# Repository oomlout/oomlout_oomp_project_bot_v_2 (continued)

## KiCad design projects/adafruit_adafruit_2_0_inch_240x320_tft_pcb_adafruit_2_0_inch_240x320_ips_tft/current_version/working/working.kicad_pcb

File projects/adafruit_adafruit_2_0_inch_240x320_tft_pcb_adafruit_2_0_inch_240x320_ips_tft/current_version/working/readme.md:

# adafruit_2_0_inch_240x320_tft_pcb
 
## summary 
* id: adafruit_adafruit_2_0_inch_240x320_tft_pcb_adafruit_2_0_inch_240x320_ips_tft
* user: adafruit
* name: adafruit_2_0_inch_240x320_tft_pcb
* board: adafruit_2_0_inch_240x320_ips_tft
* repo: https://github.com/adafruit/Adafruit-2.0-inch-240x320-TFT-PCB

* src_file_repo_sch: 
* src_file_repo_sch_link: https://github.com/adafruit/Adafruit-2.0-inch-240x320-TFT-PCB/tree/master/
* full details link: https://github.com/oomlout/oomlout_oomp_project_bot_v_2/tree/main/projects/adafruit_adafruit_2_0_inch_240x320_tft_pcb_adafruit_2_0_inch_240x320_ips_tft/current_version/working  

## schematic  
  
[schematic (pdf)](working_schematic.pdf) 

## pcb  

[board (pdf)](working.pdf)  

## working_bom
| Id | Designator | Footprint | Quantity | Designation | Supplier and ref |  | None | 
| --- | --- | --- | --- | --- | --- | --- | --- | 
| 1 | U2 | SOT23-5 | 1 | AP2112K-3.3 |  |  | [''] | 
| 2 | R1 | 0805-NO | 1 | 10 |  |  | [''] | 
| 3 | Q1 | SOT23-R | 1 | BSS138 |  |  | [''] | 
| 4 | U$24 | PCBFEAT-REV-040 | 1 |  |  |  | [''] | 
| 5 | U3 | SOIC16 | 1 | 74HC4050D |  |  | [''] | 
| 6 | FID1,FID3,FID2 | FIDUCIAL_1MM | 3 | FIDUCIAL_1MM |  |  | [''] | 
| 7 | R8,R5,R2,R7 | 0805-NO | 4 | 10K |  |  | [''] | 
| 8 | U$4,U$3 | MOUNTINGHOLE_2.5_PLATED | 2 | MOUNTINGHOLE2.5 |  |  | [''] | 
| 9 | IC4 | SOT23 | 1 | APX803-SAG |  |  | [''] | 
| 10 | JP1 | 1X11_ROUND_76 | 1 |  |  |  | [''] | 
| 11 | C1,C3,C2 | 0805-NO | 3 | 10uF |  |  | [''] | 
| 12 | CN1 | MICROSD | 1 |  |  |  | [''] | 
| 13 | U$20 | ADAFRUIT_TEXT_30MM | 1 |  |  |  | [''] | 
| 14 | DISP1 | TFT_2.0IN_240X320_12P | 1 | DISP_LCD_GENERIC_SPI_2.0IN_240X320 |  |  | [''] | 

## bom_schematic
| Ref | Qnty | Value | Cmp name | Footprint | Description | Vendor | DNP | 
| --- | --- | --- | --- | --- | --- | --- | --- | 
| C1, C2, C3 | 3 | 10uF | CAP_CERAMIC0805-NOOUTLINE | working:0805-NO |  |  |  | 
| CN1 | 1 | MICROSD | MICROSD | working:MICROSD |  |  |  | 
| DISP1 | 1 | DISP_LCD_GENERIC_SPI_2.0IN_240X320 | DISP_LCD_GENERIC_SPI_2.0IN_240X320 | working:TFT_2.0IN_240X320_12P |  |  |  | 
| FID1, FID2, FID3 | 3 | FIDUCIAL_1MM | FIDUCIAL_1MM | working:FIDUCIAL_1MM |  |  |  | 
| IC4 | 1 | APX803-SAG | AXP083-SAG | working:SOT23 |  |  |  | 
| JP1 | 1 | HEADER-1X1176MIL | HEADER-1X1176MIL | working:1X11_ROUND_76 |  |  |  | 
| Q1 | 1 | BSS138 | MOSFET-NREFLOW | working:SOT23-R |  |  |  | 
| R1 | 1 | 10 | RESISTOR0805_NOOUTLINE | working:0805-NO |  |  |  | 
| R2, R5, R7, R8 | 4 | 10K | RESISTOR0805_NOOUTLINE | working:0805-NO |  |  |  | 
| U2 | 1 | AP2112K-3.3 | VREG_SOT23-5 | working:SOT23-5 |  |  |  | 
| U3 | 1 | 74HC4050D | 74HC4050D | working:SOIC16 |  |  |  | 
| U$3, U$4 | 2 | MOUNTINGHOLE2.5 | MOUNTINGHOLE2.5 | working:MOUNTINGHOLE_2.5_PLATED |  |  |  | 

## mounting_holes
| x | y | package | value | ref | size | 
| --- | --- | --- | --- | --- | --- | 
| 30.48 | 0.0 | MOUNTINGHOLE_2.5_PLATED | MOUNTINGHOLE2.5 | U$3 | m3 | 
| 0.0 | 0.0 | MOUNTINGHOLE_2.5_PLATED | MOUNTINGHOLE2.5 | U$4 | m3 |

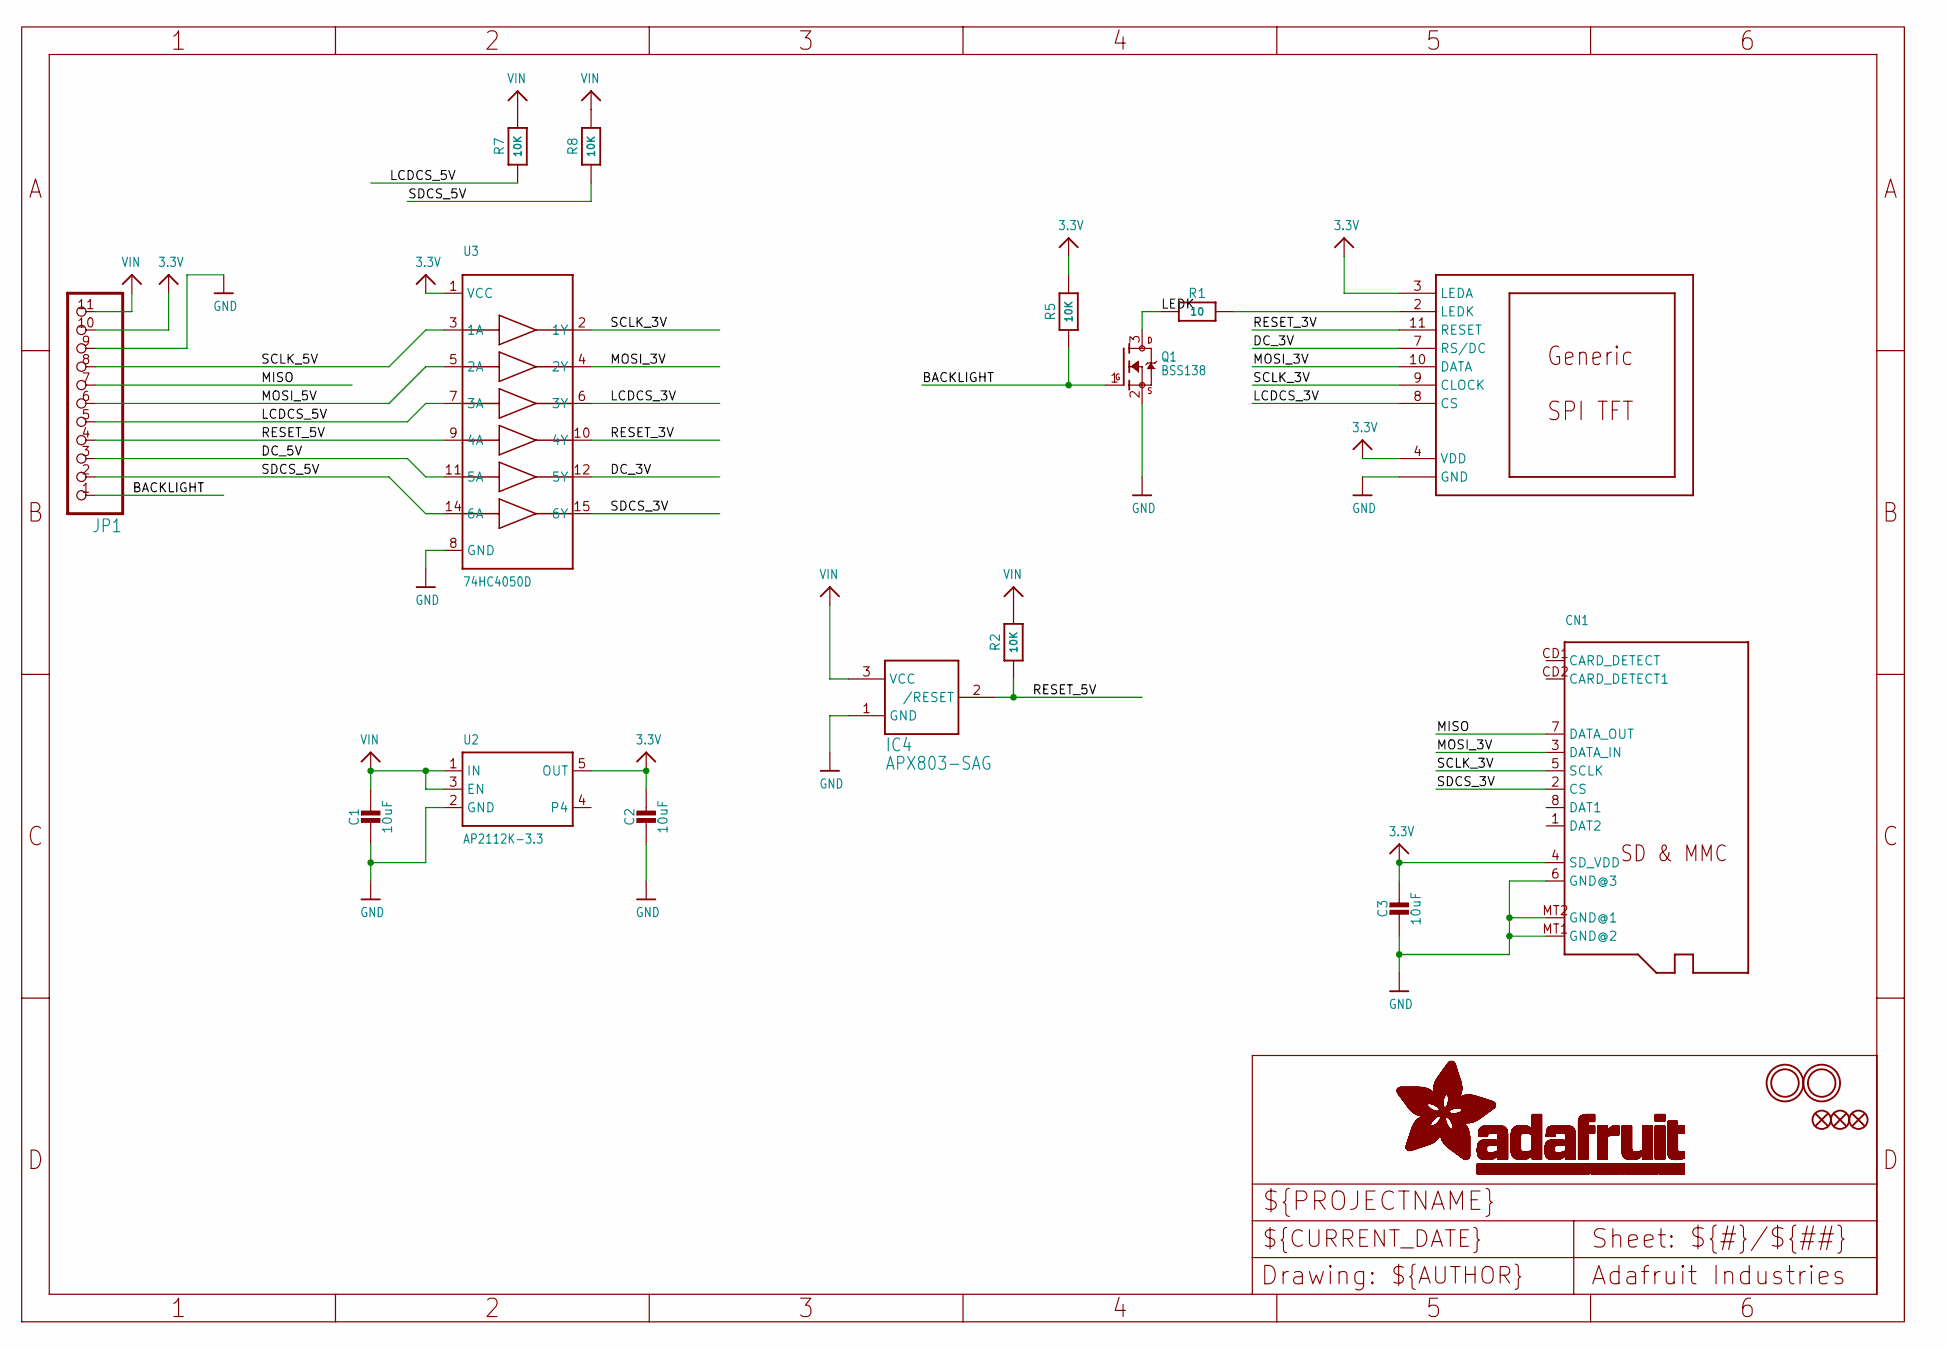
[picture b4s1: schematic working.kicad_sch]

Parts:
C1, C2, C3: 10uF; 0805-NO
CN1: MICROSD
DISP1: DISP_LCD_GENERIC_SPI_2.0IN_240X320; TFT_2.0IN_240X320_12P
FID1, FID2, FID3: FIDUCIAL_1MM
IC4: APX803-SAG; SOT23
JP1: HEADER-1X1176MIL; 1X11_ROUND_76
Q1: BSS138; SOT23-R
R1: 10; 0805-NO
R2, R5, R7, R8: 10K; 0805-NO
U2: AP2112K-3.3; SOT23-5
U3: 74HC4050D; SOIC16
U$3, U$4: MOUNTINGHOLE2.5; MOUNTINGHOLE_2.5_PLATED

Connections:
3.3V: C2.1, C3.1, CN1.4 (SD_VDD), DISP1.3 (LEDA), DISP1.4 (VDD), JP1.10, R5.2, U2.5 (OUT), U3.1 (VCC)
BACKLIGHT: JP1.1, Q1.1 (G), R5.1
DC_3V: DISP1.7 (RS/DC), U3.12 (5Y)
DC_5V: JP1.3, U3.11 (5A)
GND: C1.2, C2.2, C3.2, CN1.6 (GND@3), CN1.MT1 (GND@2), CN1.MT2 (GND@1), DISP1.1 (GND), DISP1.5 (GND), DISP1.6 (GND), DISP1.12 (GND), IC4.1 (GND), JP1.9, Q1.2 (S), U2.2 (GND), U3.8 (GND)
LCDCS_3V: DISP1.8 (CS), U3.6 (3Y)
LCDCS_5V: JP1.5, R7.1, U3.7 (3A)
LEDK: Q1.3 (D), R1.1
MISO: CN1.7 (DATA_OUT), JP1.7
MOSI_3V: CN1.3 (DATA_IN), DISP1.10 (DATA), U3.4 (2Y)
MOSI_5V: JP1.6, U3.5 (2A)
unnamed: DISP1.2 (LEDK), R1.2
RESET_3V: DISP1.11 (RESET), U3.10 (4Y)
RESET_5V: IC4.2 (/RESET), JP1.4, R2.1, U3.9 (4A)
SCLK_3V: CN1.5 (SCLK), DISP1.9 (CLOCK), U3.2 (1Y)
SCLK_5V: JP1.8, U3.3 (1A)
SDCS_3V: CN1.2 (CS), U3.15 (6Y)
SDCS_5V: JP1.2, R8.1, U3.14 (6A)
VIN: C1.1, IC4.3 (VCC), JP1.11, R2.2, R7.2, R8.2, U2.1 (IN), U2.3 (EN)

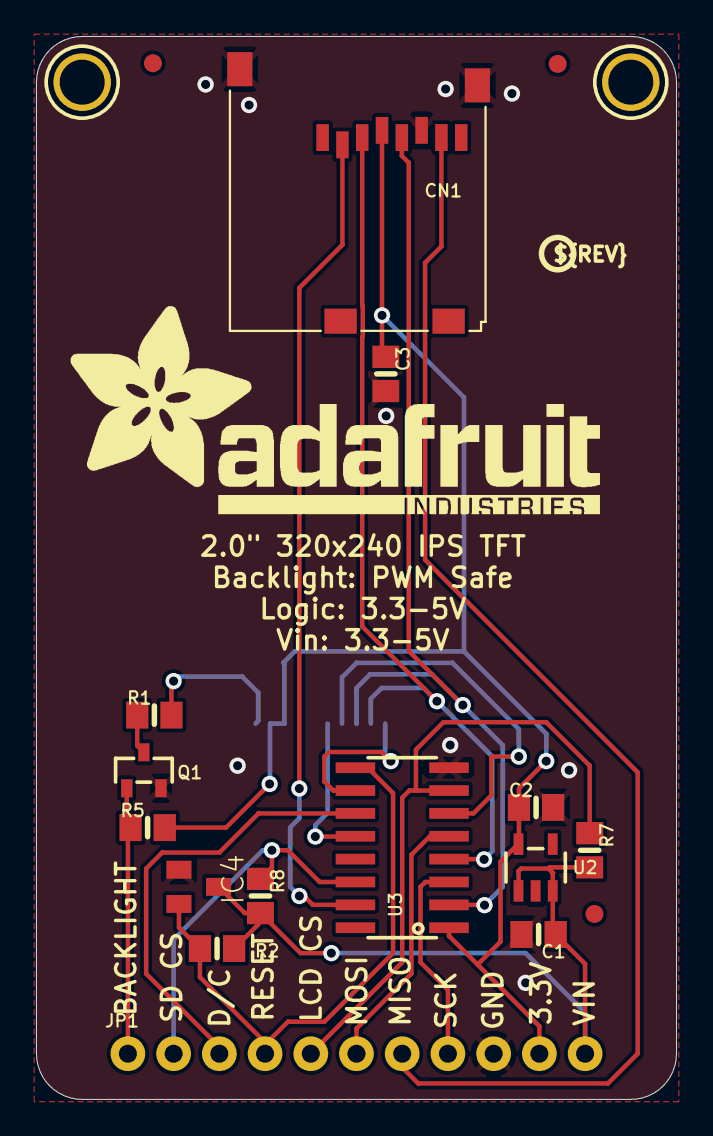
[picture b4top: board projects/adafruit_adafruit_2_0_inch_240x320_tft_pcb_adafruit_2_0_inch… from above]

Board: 2 copper layers, 35.6 x 59.1 mm, 22 parts (1 on the bottom side), 19 nets.

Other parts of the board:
U$20: ADAFRUIT_TEXT_30MM
U$24: PCBFEAT-REV-040

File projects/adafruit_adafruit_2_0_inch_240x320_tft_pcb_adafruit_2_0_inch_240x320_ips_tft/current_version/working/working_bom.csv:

"Id";"Designator";"Footprint";"Quantity";"Designation";"Supplier and ref";
1;"U2";"SOT23-5";1;"AP2112K-3.3";;;
2;"R1";"0805-NO";1;"10";;;
3;"Q1";"SOT23-R";1;"BSS138";;;
4;"U$24";"PCBFEAT-REV-040";1;"";;;
5;"U3";"SOIC16";1;"74HC4050D";;;
6;"FID1,FID3,FID2";"FIDUCIAL_1MM";3;"FIDUCIAL_1MM";;;
7;"R8,R5,R2,R7";"0805-NO";4;"10K";;;
8;"U$4,U$3";"MOUNTINGHOLE_2.5_PLATED";2;"MOUNTINGHOLE2.5";;;
9;"IC4";"SOT23";1;"APX803-SAG";;;
10;"JP1";"1X11_ROUND_76";1;"";;;
11;"C1,C3,C2";"0805-NO";3;"10uF";;;
12;"CN1";"MICROSD";1;"";;;
13;"U$20";"ADAFRUIT_TEXT_30MM";1;"";;;
14;"DISP1";"TFT_2.0IN_240X320_12P";1;"DISP_LCD_GENERIC_SPI_2.0IN_240X320";;;

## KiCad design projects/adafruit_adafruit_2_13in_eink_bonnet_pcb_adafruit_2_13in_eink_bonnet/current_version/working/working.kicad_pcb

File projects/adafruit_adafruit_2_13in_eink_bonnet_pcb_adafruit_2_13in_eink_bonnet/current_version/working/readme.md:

# adafruit_2_13in_eink_bonnet_pcb
 
## summary 
* id: adafruit_adafruit_2_13in_eink_bonnet_pcb_adafruit_2_13in_eink_bonnet
* user: adafruit
* name: adafruit_2_13in_eink_bonnet_pcb
* board: adafruit_2_13in_eink_bonnet
* repo: https://github.com/adafruit/Adafruit-2-13in-eInk-Bonnet-PCB

* src_file_repo_sch: 
* src_file_repo_sch_link: https://github.com/adafruit/Adafruit-2-13in-eInk-Bonnet-PCB/tree/master/
* full details link: https://github.com/oomlout/oomlout_oomp_project_bot_v_2/tree/main/projects/adafruit_adafruit_2_13in_eink_bonnet_pcb_adafruit_2_13in_eink_bonnet/current_version/working  

## schematic  
  
[schematic (pdf)](working_schematic.pdf) 

## pcb  

[board (pdf)](working.pdf)  

## working_bom
| Id | Designator | Footprint | Quantity | Designation | Supplier and ref |  | None | 
| --- | --- | --- | --- | --- | --- | --- | --- | 
| 1 | C3,C4,C23,C22 | 0805-NO | 4 | 1uF/25V |  |  | [''] | 
| 2 | R3,R5,R2,R6 | 0603-NO | 4 | 100K |  |  | [''] | 
| 3 | D2,D3,D1 | SOD-123 | 3 | MBR0540 |  |  | [''] | 
| 4 | C5 | 0805-NO | 1 | 4.7uF/25V |  |  | [''] | 
| 5 | U$28 | ADAFRUIT_TEXT_20MM | 1 |  |  |  | [''] | 
| 6 | C16,C24 | 0805-NO | 2 | 1uF |  |  | [''] | 
| 7 | C1,C15 | 0805-NO | 2 | 10uF/10V+ |  |  | [''] | 
| 8 | CONN2 | JST_SH4 | 1 | STEMMA_I2C_QT |  |  | [''] | 
| 9 | Q5 | SOT23-3 | 1 | IRLML0100 |  |  | [''] | 
| 10 | C2,C6 | 0805-NO | 2 | 1uF/10V |  |  | [''] | 
| 11 | R4 | 0805_10MGAP | 1 | 0.47ohm |  |  | [''] | 
| 12 | U$30 | STEMMAQT | 1 |  |  |  | [''] | 
| 13 | U$9 | PCBFEAT-REV-040 | 1 |  |  |  | [''] | 
| 14 | U$29 | THINKINK_1.25IN | 1 |  |  |  | [''] | 
| 15 | FID4,FID1,FID3,FID2 | FIDUCIAL_1MM | 4 | FIDUCIAL_1MM |  |  | [''] | 
| 16 | C21 | 0805-NO | 1 | 10ÂµF |  |  | [''] | 
| 17 | L1 | INDUCTOR_4X4MM_NR401 | 1 | 10uH |  |  | [''] | 
| 18 | SW3,SW4 | TACTILE_3X6MM | 2 |  |  |  | [''] | 
| 19 | RPI2 | PI_BONNET_SMT_NODIM | 1 | RASPBERRYPI_BPLUS_SMT_NODIM |  |  | [''] | 
| 20 | EINK1 | EINK_213IN_104X212 | 1 | EINK_24PIN_213IN |  |  | [''] | 

## bom_schematic
| Ref | Qnty | Value | Cmp name | Footprint | Description | Vendor | DNP | 
| --- | --- | --- | --- | --- | --- | --- | --- | 
| C1, C15 | 2 | 10uF/10V+ | CAP_CERAMIC0805-NOOUTLINE | working:0805-NO |  |  |  | 
| C2, C6 | 2 | 1uF/10V | CAP_CERAMIC0805-NOOUTLINE | working:0805-NO |  |  |  | 
| C3, C4, C22, C23 | 4 | 1uF/25V | CAP_CERAMIC0805-NOOUTLINE | working:0805-NO |  |  |  | 
| C5 | 1 | 4.7uF/25V | CAP_CERAMIC0805-NOOUTLINE | working:0805-NO |  |  |  | 
| C16, C24 | 2 | 1uF | CAP_CERAMIC0805-NOOUTLINE | working:0805-NO |  |  |  | 
| C21 | 1 | 10ÂµF | CAP_CERAMIC0805-NOOUTLINE | working:0805-NO |  |  |  | 
| CONN2 | 1 | STEMMA_I2C_QT | STEMMA_I2C_QT | working:JST_SH4 |  |  |  | 
| D1, D2, D3 | 3 | MBR0540 | DIODE-SCHOTTKYSOD-123 | working:SOD-123 |  |  |  | 
| EINK1 | 1 | EINK_24PIN_213IN | EINK_24PIN_213IN | working:EINK_213IN_104X212 |  |  |  | 
| FID1, FID2, FID3, FID4 | 4 | FIDUCIAL_1MM | FIDUCIAL_1MM | working:FIDUCIAL_1MM |  |  |  | 
| L1 | 1 | 10uH | INDUCTORNR401 | working:INDUCTOR_4X4MM_NR401 |  |  |  | 
| Q5 | 1 | IRLML2060TRPBF | IRLML2060TRPBF | working:SOT23-3 |  |  |  | 
| R2, R3, R5, R6 | 4 | 100K | RESISTOR_0603_NOOUT | working:0603-NO |  |  |  | 
| R4 | 1 | 0.47ohm | RESISTOR0805_10MGAP | working:0805_10MGAP |  |  |  | 
| RPI2 | 1 | RASPBERRYPI_BPLUS_SMT_NODIM | RASPBERRYPI_BPLUS_SMT_NODIM | working:PI_BONNET_SMT_NODIM |  |  |  | 
| SW3, SW4 | 2 | SWITCH_PUSHBUTTON_3.5X6MM | SWITCH_PUSHBUTTON_3.5X6MM | working:TACTILE_3X6MM |  |  |  |

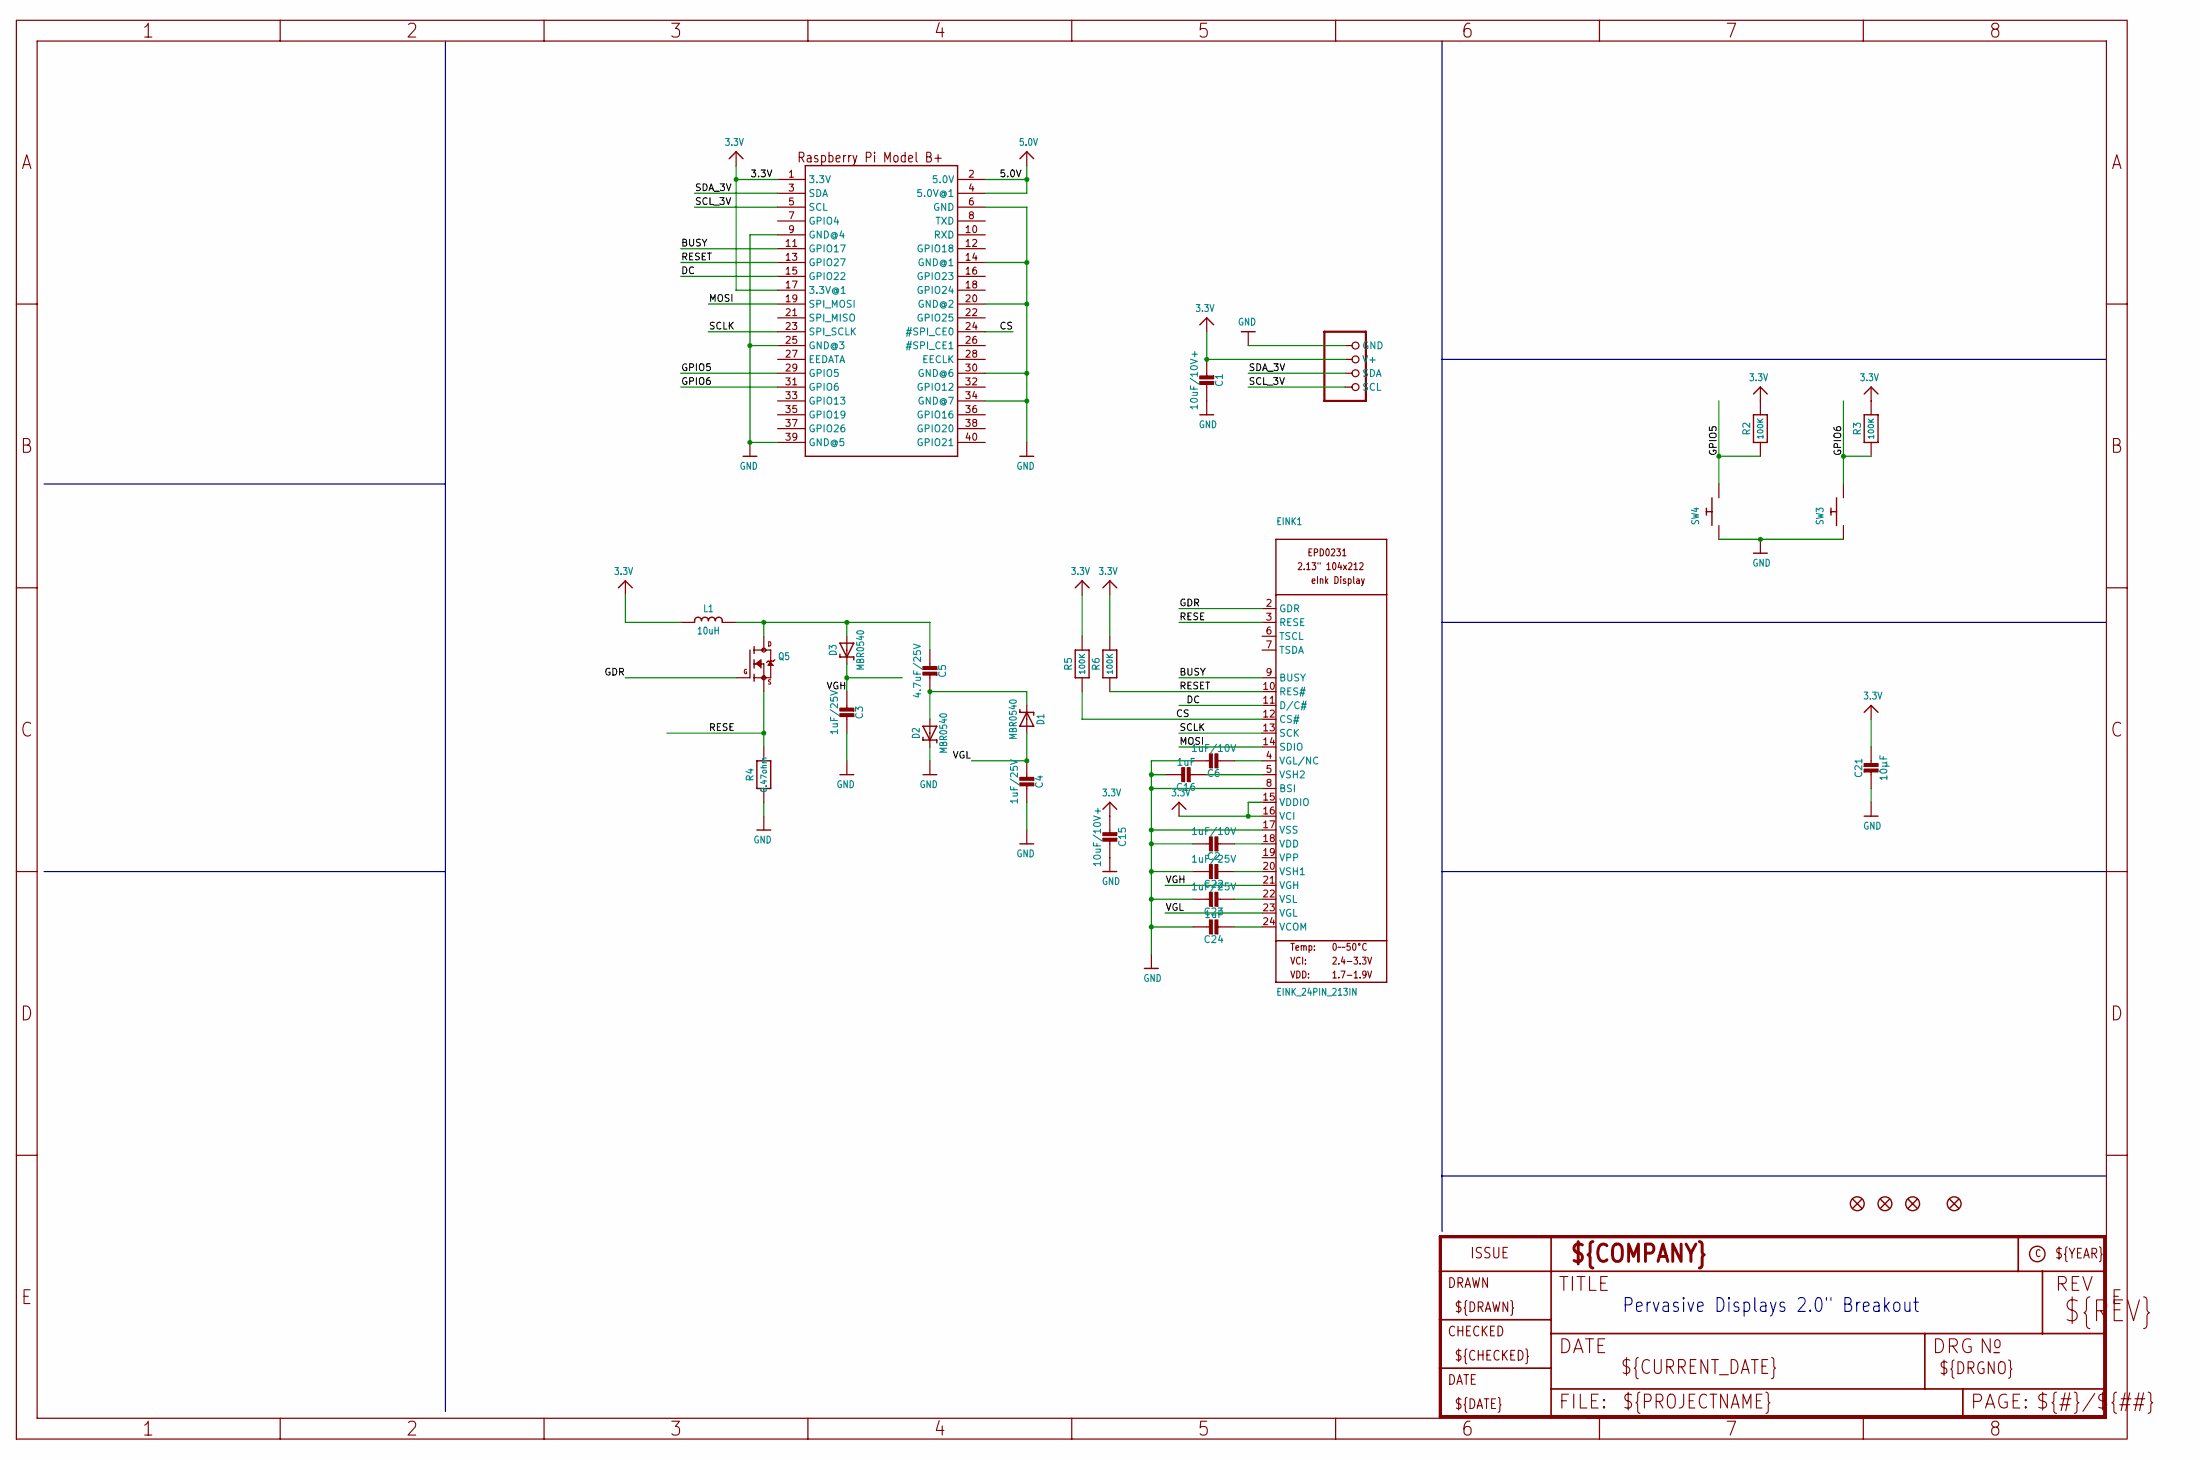
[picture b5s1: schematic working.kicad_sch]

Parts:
C1, C15: 10uF/10V+; 0805-NO
C2, C6: 1uF/10V; 0805-NO
C3, C4, C22, C23: 1uF/25V; 0805-NO
C5: 4.7uF/25V; 0805-NO
C16, C24: 1uF; 0805-NO
C21: 10µF; 0805-NO
CONN2: STEMMA_I2C_QT; JST_SH4
D1, D2, D3: MBR0540; SOD-123
EINK1: EINK_24PIN_213IN; EINK_213IN_104X212
FID1, FID2, FID3, FID4: FIDUCIAL_1MM
L1: 10uH; INDUCTOR_4X4MM_NR401
Q5: IRLML2060TRPBF; SOT23-3
R2, R3, R5, R6: 100K; 0603-NO
R4: 0.47ohm; 0805_10MGAP
RPI2: RASPBERRYPI_BPLUS_SMT_NODIM; PI_BONNET_SMT_NODIM
SW3, SW4: SWITCH_PUSHBUTTON_3.5X6MM; TACTILE_3X6MM

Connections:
3.3V: C1.2, C15.2, C21.1, CONN2.2 (V+), EINK1.15 (VDDIO), EINK1.16 (VCI), L1.P$2 (2), R2.2, R3.2, R5.2, R6.2, RPI2.1 (3.3V), RPI2.17 (3.3V@1)
5.0V: RPI2.2 (5.0V), RPI2.4 (5.0V@1)
BUSY: EINK1.9 (BUSY), RPI2.11 (GPIO17)
CS: EINK1.12 (CS#), R5.1, RPI2.24 (#SPI_CE0)
DC: EINK1.11 (D/C#), RPI2.15 (GPIO22)
GDR: EINK1.2 (GDR), Q5.1 (G)
GND: C1.1, C2.1, C3.2, C4.2, C6.1, C15.1, C16.1, C21.2, C22.1, C23.1, C24.1, CONN2.1 (GND), D2.C, EINK1.8 (BSI), EINK1.17 (VSS), R4.2, RPI2.6 (GND), RPI2.9 (GND@4), RPI2.14 (GND@1), RPI2.20 (GND@2), RPI2.25 (GND@3), RPI2.30 (GND@6), RPI2.34 (GND@7), RPI2.39 (GND@5), SW3.P$1, SW4.P$1
GPIO5: R2.1, RPI2.29 (GPIO5), SW4.P$2
GPIO6: R3.1, RPI2.31 (GPIO6), SW3.P$2
MOSI: EINK1.14 (SDIO), RPI2.19 (SPI_MOSI)
unnamed: C5.2, D1.C, D2.A
unnamed: C5.1, D3.A, L1.P$1 (1), Q5.3 (D)
unnamed: C16.2, EINK1.5 (VSH2)
unnamed: C2.2, EINK1.18 (VDD)
unnamed: C22.2, EINK1.20 (VSH1)
unnamed: C6.2, EINK1.4 (VGL/NC)
unnamed: C23.2, EINK1.22 (VSL)
unnamed: C24.2, EINK1.24 (VCOM)
RESE: EINK1.3 (RESE), Q5.2 (S), R4.1
RESET: EINK1.10 (RES#), R6.1, RPI2.13 (GPIO27)
SCLK: EINK1.13 (SCK), RPI2.23 (SPI_SCLK)
SCL_3V: CONN2.4 (SCL), RPI2.5 (SCL)
SDA_3V: CONN2.3 (SDA), RPI2.3 (SDA)
VGH: C3.1, D3.C, EINK1.21 (VGH)
VGL: C4.1, D1.A, EINK1.23 (VGL)

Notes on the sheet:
Pervasive Displays 2.0" Breakout

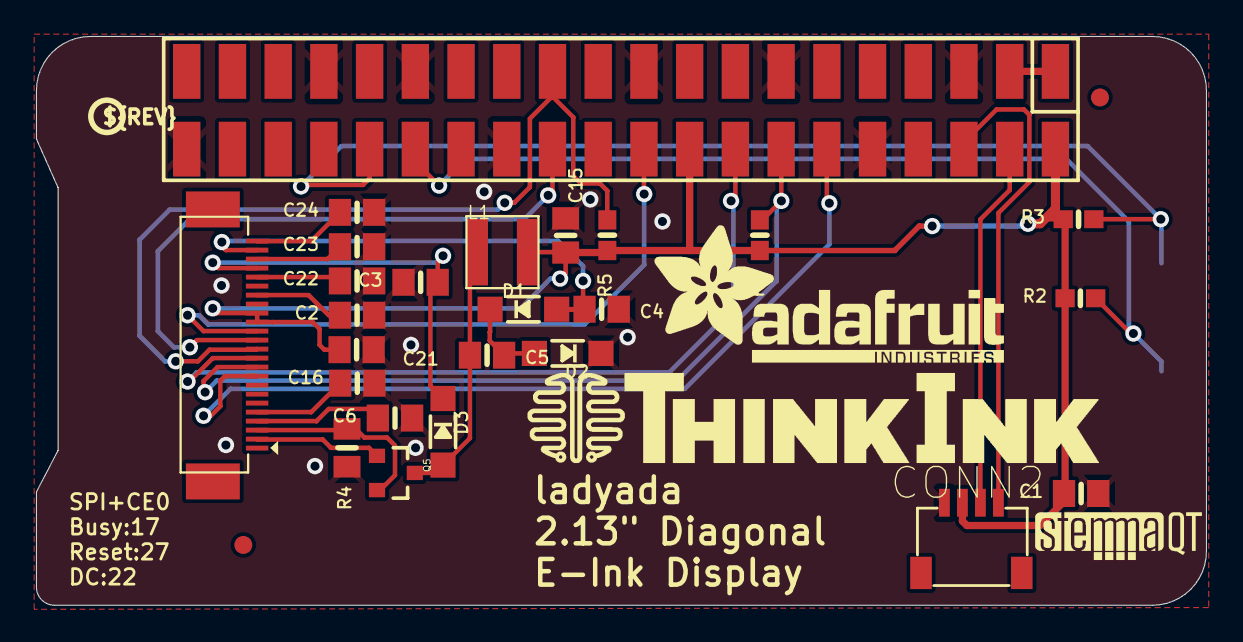
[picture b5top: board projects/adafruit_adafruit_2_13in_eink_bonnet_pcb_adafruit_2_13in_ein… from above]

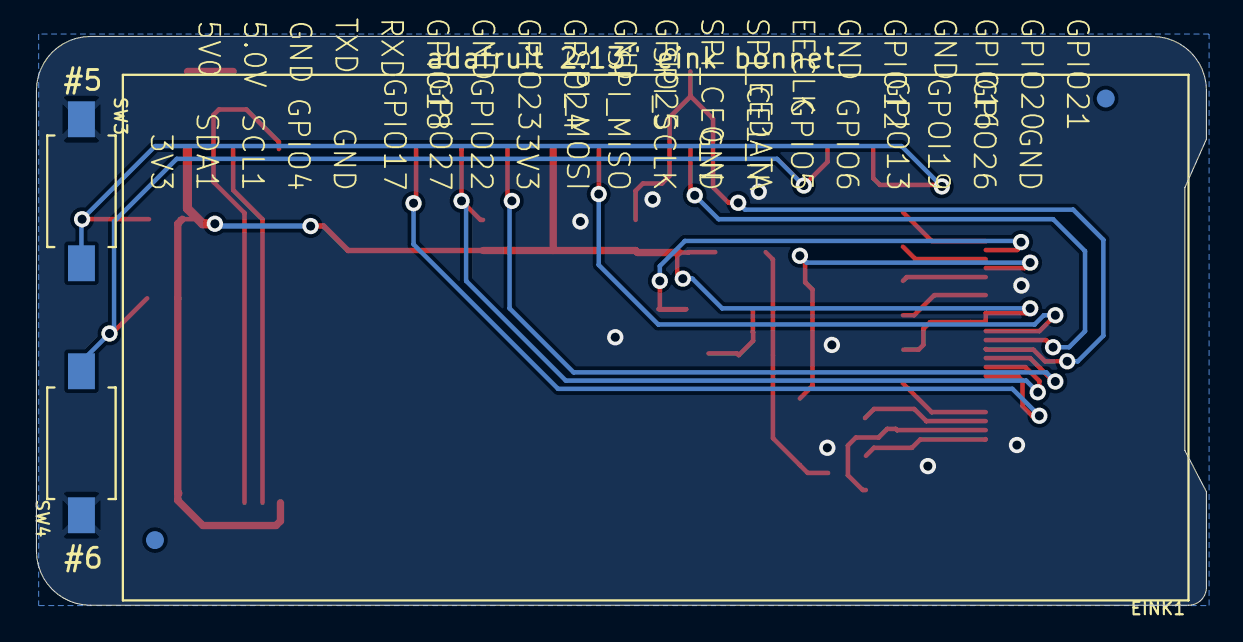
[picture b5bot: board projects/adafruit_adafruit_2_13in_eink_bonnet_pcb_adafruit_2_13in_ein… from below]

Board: 2 copper layers, 65.0 x 31.6 mm, 35 parts (6 on the bottom side), 25 nets.

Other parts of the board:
U$9: PCBFEAT-REV-040
U$28: ADAFRUIT_TEXT_20MM
U$29: THINKINK_1.25IN
U$30: STEMMAQT

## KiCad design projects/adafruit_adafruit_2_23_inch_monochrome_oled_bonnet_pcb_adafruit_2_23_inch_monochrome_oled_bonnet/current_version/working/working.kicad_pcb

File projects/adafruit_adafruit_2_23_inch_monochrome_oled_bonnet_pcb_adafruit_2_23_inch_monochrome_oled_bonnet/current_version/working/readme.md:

# adafruit_2_23_inch_monochrome_oled_bonnet_pcb
 
## summary 
* id: adafruit_adafruit_2_23_inch_monochrome_oled_bonnet_pcb_adafruit_2_23_inch_monochrome_oled_bonnet
* user: adafruit
* name: adafruit_2_23_inch_monochrome_oled_bonnet_pcb
* board: adafruit_2_23_inch_monochrome_oled_bonnet
* repo: https://github.com/adafruit/Adafruit-2.23-inch-Monochrome-OLED-Bonnet-PCB

* src_file_repo_sch: 
* src_file_repo_sch_link: https://github.com/adafruit/Adafruit-2.23-inch-Monochrome-OLED-Bonnet-PCB/tree/master/
* full details link: https://github.com/oomlout/oomlout_oomp_project_bot_v_2/tree/main/projects/adafruit_adafruit_2_23_inch_monochrome_oled_bonnet_pcb_adafruit_2_23_inch_monochrome_oled_bonnet/current_version/working  

## schematic  
  
[schematic (pdf)](working_schematic.pdf) 

## pcb  

[board (pdf)](working.pdf)  

## working_bom
| Id | Designator | Footprint | Quantity | Designation | Supplier and ref |  | None | 
| --- | --- | --- | --- | --- | --- | --- | --- | 
| 1 | RPI1 | PI_BONNET_SMT | 1 | RASPBERRYPI_BPLUS_BONNETSMT |  |  | [''] | 
| 2 | U$11 | STEMMAQT | 1 |  |  |  | [''] | 
| 3 | U$33 | 2.23OLED_BOTTOM_CONTACT | 1 | 2.23_INCH_OLEDBOTTOM_CONTACT_24_PIN_OLED |  |  | [''] | 
| 4 | C9,C1 | 0603-NO | 2 | 0.1uF |  |  | [''] | 
| 5 | C8,C2,C6,C5,C4 | 0805-NO | 5 | 10uF |  |  | [''] | 
| 6 | R2,R1,R8 | 0603-NO | 3 | 10K |  |  | [''] | 
| 7 | R3 | 0805-NO | 1 | 910K |  |  | [''] | 
| 8 | IC1 | SOT23 | 1 | APX803S-29SA |  |  | [''] | 
| 9 | CONN1 | JST_SH4 | 1 | STEMMA_I2C_QT |  |  | [''] | 
| 10 | D4 | SOD-123 | 1 | MBR120 |  |  | [''] | 
| 11 | SJ1 | SOLDERJUMPER_ARROW_NOPASTE | 1 |  |  |  | [''] | 
| 12 | C7 | 0805-NO | 1 | 2.2uF |  |  | [''] | 
| 13 | U1 | SOT23-5 | 1 | FAN5331 |  |  | [''] | 
| 14 | R7 | 0603-NO | 1 | 100K |  |  | [''] | 
| 15 | L1 | INDUCTOR_1007 | 1 | 10uH |  |  | [''] | 
| 16 | U$2 | PCBFEAT-REV-040 | 1 |  |  |  | [''] | 

## bom_schematic
| Ref | Qnty | Value | Cmp name | Footprint | Description | Vendor | DNP | 
| --- | --- | --- | --- | --- | --- | --- | --- | 
| C1, C9 | 2 | 0.1uF | CAP_CERAMIC0603_NO | working:0603-NO |  |  |  | 
| C2, C4, C5, C6, C8 | 5 | 10uF | CAP_CERAMIC0805-NOOUTLINE | working:0805-NO |  |  |  | 
| C7 | 1 | 2.2uF | CAP_CERAMIC0805-NOOUTLINE | working:0805-NO |  |  |  | 
| CONN1 | 1 | STEMMA_I2C_QT | STEMMA_I2C_QT | working:JST_SH4 |  |  |  | 
| D4 | 1 | MBR120 | DIODESOD-123 | working:SOD-123 |  |  |  | 
| IC1 | 1 | APX803S-29SA | AXP083-SAG | working:SOT23 |  |  |  | 
| L1 | 1 | 10uH | INDUCTOR | working:INDUCTOR_1007 |  |  |  | 
| R1, R2, R8 | 3 | 10K | RESISTOR_0603_NOOUT | working:0603-NO |  |  |  | 
| R3 | 1 | 910K | RESISTOR0805_NOOUTLINE | working:0805-NO |  |  |  | 
| R7 | 1 | 100K | RESISTOR_0603_NOOUT | working:0603-NO |  |  |  | 
| RPI1 | 1 | RASPBERRYPI_BPLUS_BONNETSMT | RASPBERRYPI_BPLUS_BONNETSMT | working:PI_BONNET_SMT |  |  |  | 
| SJ1 | 1 | SOLDERJUMPER | SOLDERJUMPER | working:SOLDERJUMPER_ARROW_NOPASTE |  |  |  | 
| U1 | 1 | FAN5331 | VREG_FAN5331 | working:SOT23-5 |  |  |  | 
| U$33 | 1 | 2.23_INCH_OLEDBOTTOM_CONTACT_24_PIN_OLED | 2.23_INCH_OLEDBOTTOM_CONTACT_24_PIN_OLED | working:2.23OLED_BOTTOM_CONTACT |  |  |  |

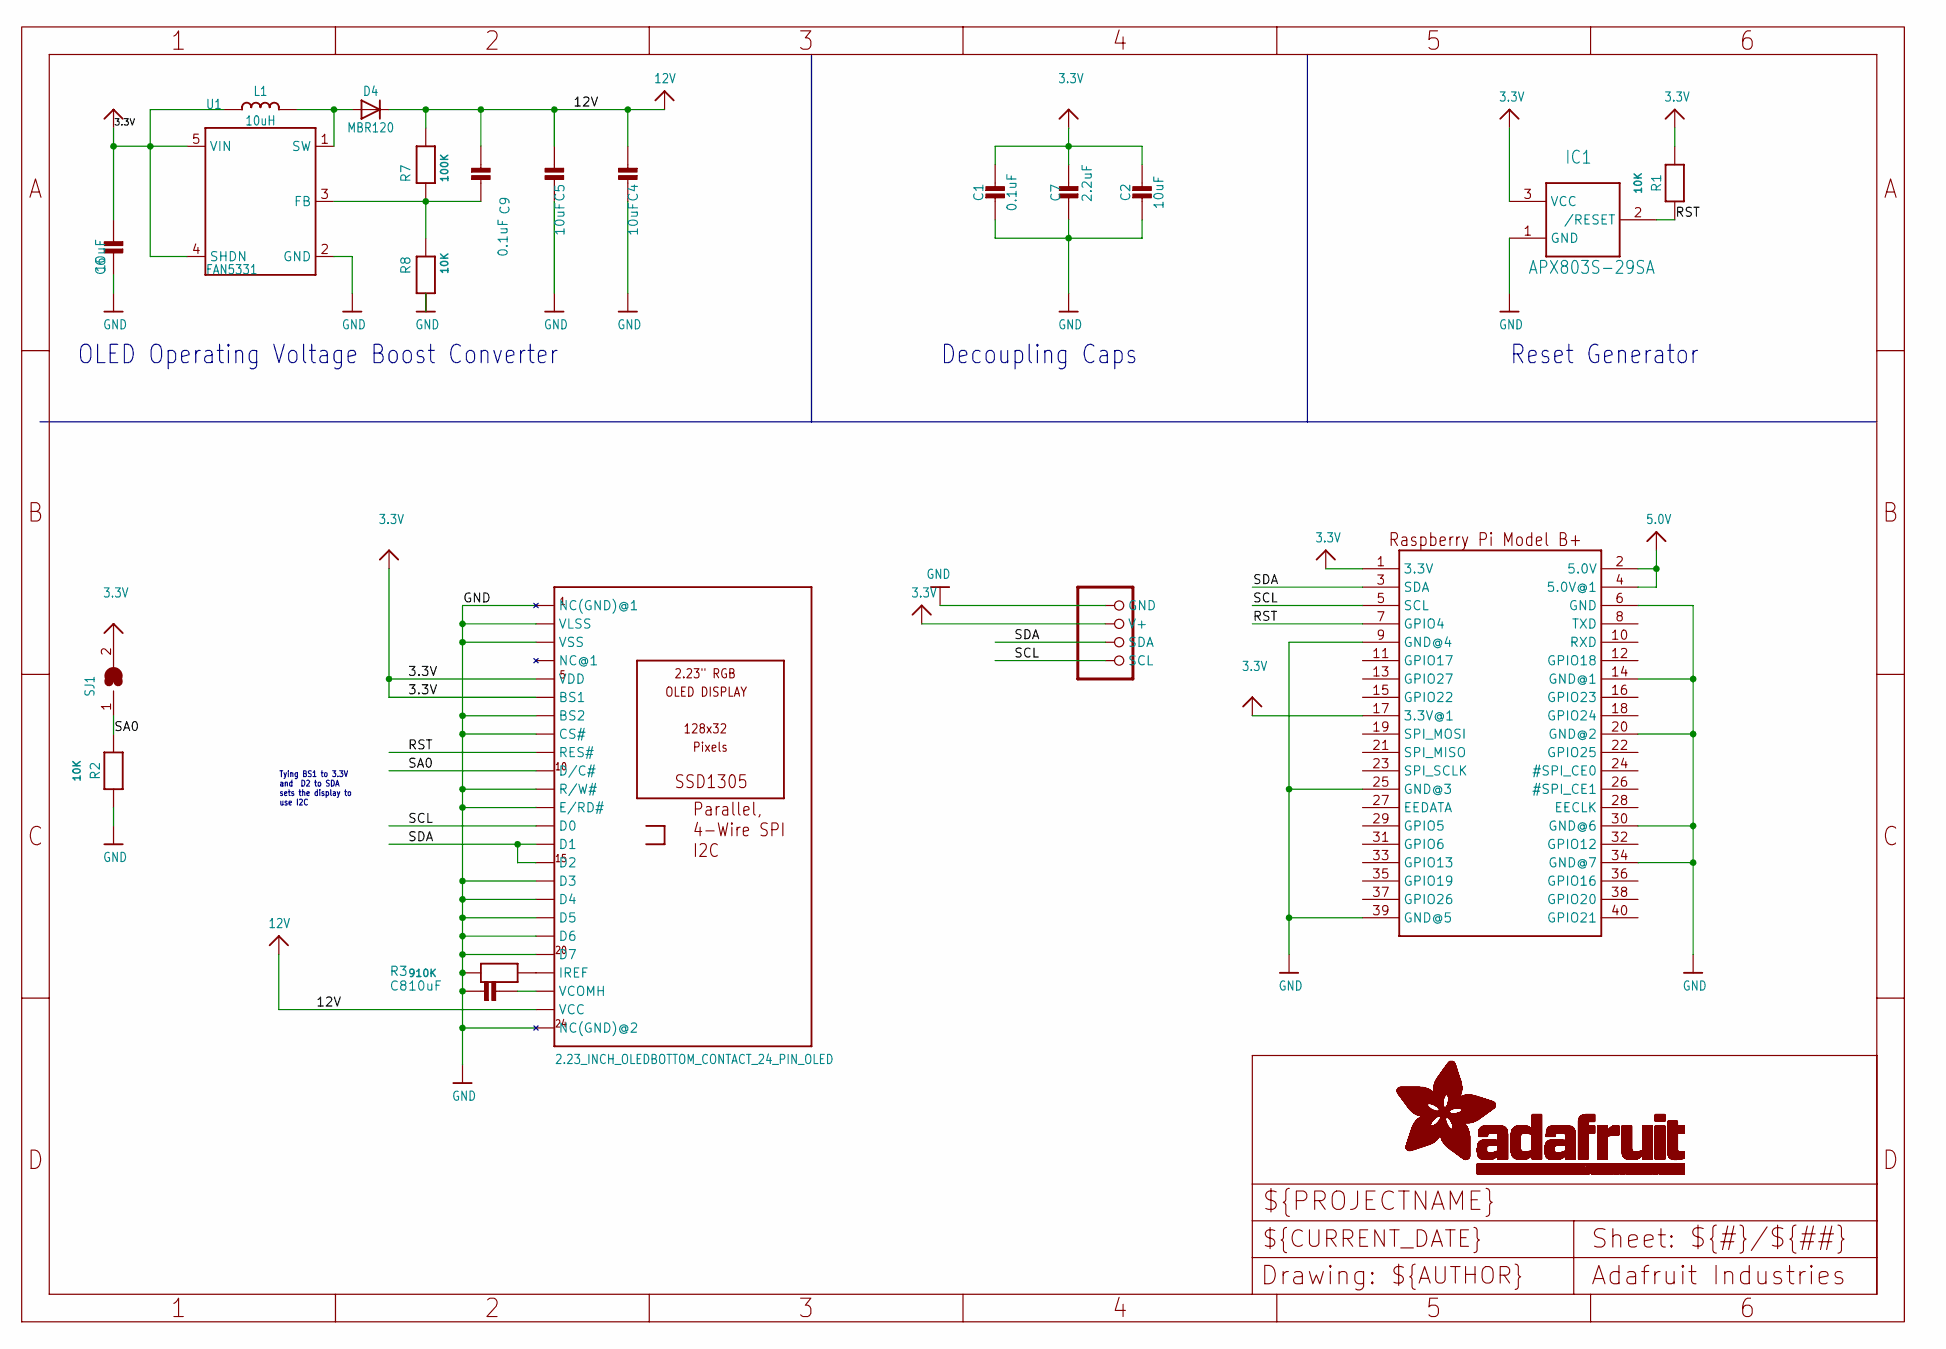
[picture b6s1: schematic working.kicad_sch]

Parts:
C1, C9: 0.1uF; 0603-NO
C2, C4, C5, C6, C8: 10uF; 0805-NO
C7: 2.2uF; 0805-NO
CONN1: STEMMA_I2C_QT; JST_SH4
D4: MBR120; SOD-123
IC1: APX803S-29SA; SOT23
L1: 10uH; INDUCTOR_1007
R1, R2, R8: 10K; 0603-NO
R3: 910K; 0805-NO
R7: 100K; 0603-NO
RPI1: RASPBERRYPI_BPLUS_BONNETSMT; PI_BONNET_SMT
SJ1: SOLDERJUMPER; SOLDERJUMPER_ARROW_NOPASTE
U1: FAN5331; SOT23-5
U$33: 2.23_INCH_OLEDBOTTOM_CONTACT_24_PIN_OLED; 2.23OLED_BOTTOM_CONTACT

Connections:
3.3V: C1.1, C2.1, C6.2, C7.2, CONN1.2 (V+), IC1.3 (VCC), L1.P$1 (1), R1.2, RPI1.1 (3.3V), RPI1.17 (3.3V@1), SJ1.2, U1.4 (SHDN), U1.5 (VIN), U$33.5 (VDD), U$33.6 (BS1)
5.0V: RPI1.2 (5.0V), RPI1.4 (5.0V@1)
12V: C4.2, C5.2, C9.1, D4.C, R7.2, U$33.23 (VCC)
GND: C1.2, C2.2, C4.1, C5.1, C6.1, C7.1, C8.1, CONN1.1 (GND), IC1.1 (GND), R2.1, R3.1, R8.1, RPI1.6 (GND), RPI1.9 (GND@4), RPI1.14 (GND@1), RPI1.20 (GND@2), RPI1.25 (GND@3), RPI1.30 (GND@6), RPI1.34 (GND@7), RPI1.39 (GND@5), U1.2 (GND), U$33.1 (NC(GND)@1), U$33.2 (VLSS), U$33.3 (VSS), U$33.7 (BS2), U$33.8 (CS#), U$33.11 (R/W#), U$33.12 (E/RD#), U$33.16 (D3), U$33.17 (D4), U$33.18 (D5), U$33.19 (D6), U$33.20 (D7), U$33.24 (NC(GND)@2), U$33.SPRT1 (NC(GND)@1), U$33.SPRT2 (NC(GND)@1)
unnamed: R3.2, U$33.21 (IREF)
unnamed: D4.A, L1.P$2 (2), U1.1 (SW)
unnamed: C9.2, R7.1, R8.2, U1.3 (FB)
unnamed: C8.2, U$33.22 (VCOMH)
RST: IC1.2 (/RESET), R1.1, RPI1.7 (GPIO4), U$33.9 (RES#)
SA0: R2.2, SJ1.1, U$33.10 (D/C#)
SCL: CONN1.4 (SCL), RPI1.5 (SCL), U$33.13 (D0)
SDA: CONN1.3 (SDA), RPI1.3 (SDA), U$33.14 (D1), U$33.15 (D2)

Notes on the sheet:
OLED Operating Voltage Boost Converter
Tying BS1 to 3.3V and D2 to SDA sets the display to use I2C
Reset Generator
Decoupling Caps

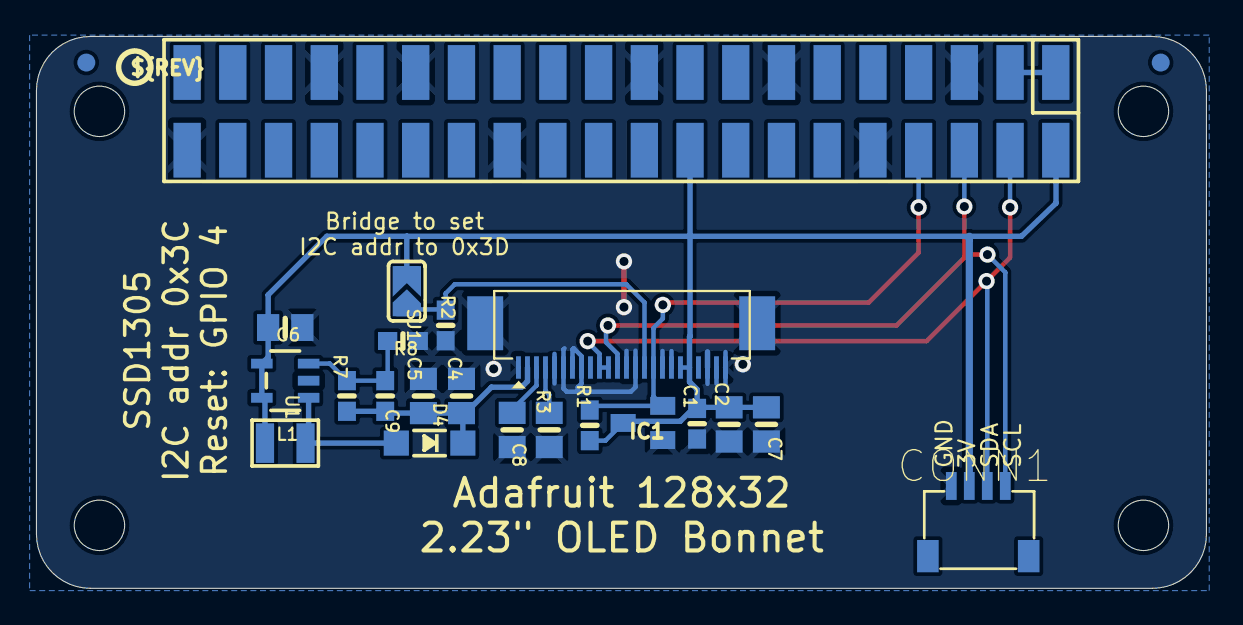
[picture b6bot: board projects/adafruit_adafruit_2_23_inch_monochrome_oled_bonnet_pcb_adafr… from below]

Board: 2 copper layers, 65.0 x 30.7 mm, 23 parts (20 on the bottom side), 12 nets.

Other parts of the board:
U$2: PCBFEAT-REV-040
U$11: STEMMAQT
